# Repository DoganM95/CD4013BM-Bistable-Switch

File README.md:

# Intro

A pcb with a single button, which on each press toggles a mosfet's output on/off, acting like a mechanical switch. 

## PCB

<table>
  <tr>
    <td>
      
    </td>
    <td>
      
    </td>
    <td>
      
    </td>
    <td>
      
    </td>
  </tr>
</table>

## Specs

- Current troughput theoretically: around 10A
- PCB input voltage: 3.0V - 5.0V
- Thicc exposed mosfet traces to create solder wires

## Properties

- Power consumption
  - Switched off:
    - 0.0 uA @ 2.5 V (= less than 100 nA)
    - 4 uA @ 4.2 V
    - 25 uA @ 5.0 V
  - Switched on:
    - 240 uA @ 2.5V
    - 500 uA @ 4.2V
    - 500 uA @ 5.0 V
- Initial state is off
- Two n-channel mosfets in parallel for high current support
- Green status led (optional)
- Debounced button

## BOM
R1: 0805 sized, 10k
R2: 0805 sized, 10k
R3: 0805 sized, 10k
C1: 0805 sized, 100nF
C2: 0805 sized, 100nF
U1: SOIC14 package, CD4013BM
U2: sot23-3 package, AO3400
U3: sot23-3 package, AO3400
S1: Tactile switch CK (Metal shell)
D1: 3528 sized, RGB led with common VCC

## Usage

- Connect e.g. a li-ion battery's GND to the pcb's GND
- Connect li-ion VCC to pcb's VCC
- Connect li-ion VCC to e.g. a motor's VCC
- Connect pcb's DR to motor's GND

## Schematic

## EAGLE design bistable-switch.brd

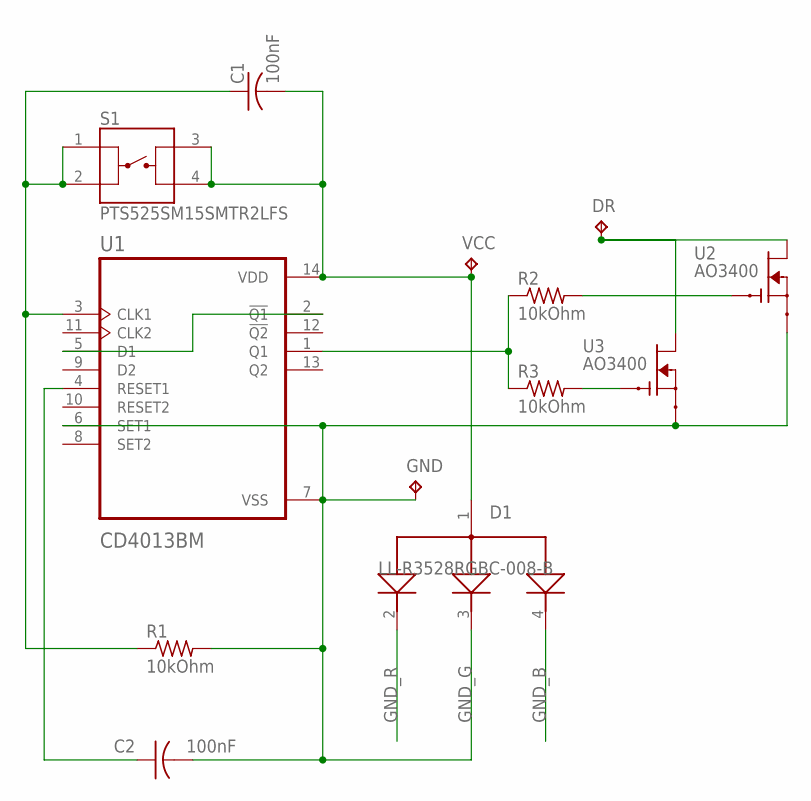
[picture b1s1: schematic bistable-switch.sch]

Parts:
C1, C2: 100nF; C0805
D1: LL-R3528RGBC-008-B; LED_LL-R3528RGBC-008-B
DR: TPB1,27; B1,27
GND: TPB1,27; B1,27
R1, R2, R3: 10kOhm; R0805
S1: PTS525SM15SMTR2LFS; SW_PTS525SM15SMTR2LFS
U1: CD4013BM; SOIC127P600X175-14N
U2, U3: AO3400; SOT23
VCC: TPB1,27; B1,27

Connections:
CLK1: C1.1, R1.1, S1.1, S1.2, U1.3 (CLK1)
DRAIN: DR.TP, U2.3 (D), U3.3 (D)
GATE_1: R2.2, U2.1 (G)
GATE_2: R3.2, U3.1 (G)
GND_B: D1.4 (CATHODE_BLUE)
GND_G: C2.2, D1.3 (CATHODE_GREEN), GND.TP, R1.2, U1.6 (SET1), U1.7 (VSS), U2.2 (S), U3.2 (S)
GND_R: D1.2 (CATHODE_RED)
unnamed: U1.2 (!Q1), U1.5 (D1)
Q1: R2.1, R3.1, U1.1 (Q1)
RST1: C2.1, U1.4 (RESET1)
VDD: C1.2, D1.1 (COMM_ANODE), S1.3, S1.4, U1.14 (VDD), VCC.TP

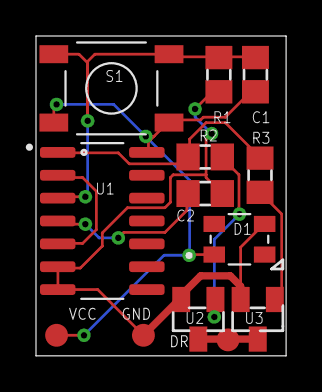
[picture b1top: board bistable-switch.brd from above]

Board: 2 copper layers, 13.9 x 17.8 mm, 13 parts (0 on the bottom side), 9 nets.

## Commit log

2024-08-15 ignore stuff
2024-08-15 init pcb v0.9 (prototype)
2024-12-07 update pcb
2024-12-07 add assets
2024-12-07 create initial release
